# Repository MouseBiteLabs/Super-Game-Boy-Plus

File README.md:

# Super Game Boy Plus (SGB+) QOL/Bugfix Branch

[MouseBiteLabs](https://github.com/MouseBiteLabs) designed a neat retro hardware project, the [Super Game Boy Plus](https://github.com/MouseBiteLabs/Super-Game-Boy-Plus) that took the proprietary components from a Super Game Boy and allowed the user to not only install a 4.194MHz crystal to fix the timing issues the 4.295MHz clock from the SNES introduced, but also to allow the user to Over- and Under-clock the system at will using button presses.  I thought that was brilliant, but a few things stood out to me.

- First, I prefer to use an 8bitdo SN30 controller, and one of the things that this controller does is allow the user to turn it off by holding [START] for several seconds.  This conflicts with the SGB+ clock alteration function.
- Secondly, the length of time necessary to hold the buttons was flow-breaking; having to hold [SELECT], wait a second, and then hold [START] for another second was _annoying_.  Plus, the 'hold to fast-forward/rewind' thing is cute, but not really meaningful when you only have a couple of clockdivs one way or the other.
- Thirdly, there is a bug or oversight in the original firmware, where employing the Clock Reset function (holding both [SELECT] and [START] for 5 seconds resets the clock to baseline) causes that state to be persistent - use it, and you won't be able to alter clock timing until you power cycle the SGB+.

Neither of these first two are _critical issues_, but I think they can be much more user-friendly.  The third is definitely an annoyance.

In this fork, I've included the original project files, as well as **SGB_Clock_Control_Tap_ALTERED.ino**, which can be written to an ATTINY85 using an AVR-capable Arduino Uno (my recommendation is the r3 Uno; don't make the same mistake I did and grab the Uno Q - it's ARM-based and can't address ATTINY stuff as a programmer).

The chief differences in my **SGB_Clock_Control_Tap_ALTERED.ino** file:

- Over/Underclock done by holding [SELECT/START] and _tapping_ the other.
- Clock Reset timing reduced to 2500ms from 5000ms.
- Clock Reset no longer continuously triggers once activated; once Clock Reset occurs, it resets itself, allowing for as much time-based shenanigans as one would care.

- Full credit for the project, design, and the vast majority of the code go to [MouseBiteLabs](https://github.com/MouseBiteLabs); all I did was riff on his project and fix a few things to my liking.

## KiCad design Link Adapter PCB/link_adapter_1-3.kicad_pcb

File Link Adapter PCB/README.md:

# Link Adapter PCB

Use this board to center the link port properly in SNES shells that *aren't* the SGB2.

NOTE: This only works on the North American Super Game Boy shell. It will not fit in a Super Famicom or PAL region SGB.

## Board Characteristics and Order Information

The zipped folder contains all the gerber files for this board. The board characteristics don't really matter a whole lot, but I would err on the thicker side for support purposes.

- Thickness: any
- Layers: 2
- Surface Finish: any

<a href="https://oshpark.com/shared_projects/MZ2FDhuA">Also available on OSH Park.</a>

## Board Explanation

Please review the main guide for instructions on how to install the board. Here is a quick reference for the board to help you keep it straight, and to not install it incorrectly.

## License

<br />This work is licensed under a <a rel="license" href="http://creativecommons.org/licenses/by-sa/4.0/">Creative Commons Attribution-ShareAlike 4.0 International License</a>. You are able to copy and redistribute the material in any medium or format, as well as remix, transform, or build upon the material for any purpose (even commercial) - but you **must** give appropriate credit, provide a link to the license, and indicate if any changes were made.

©MouseBiteLabs 2024

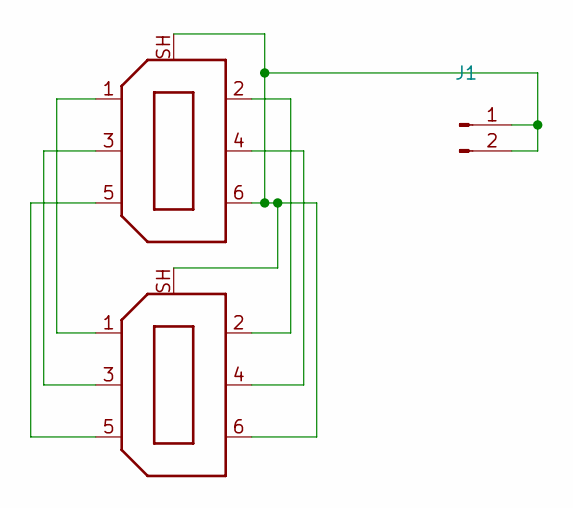
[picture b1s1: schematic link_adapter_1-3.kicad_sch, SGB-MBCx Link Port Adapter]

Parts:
J1: Conn_01x02_Pin; PinHeader_1x02_P2.54mm_Vertical
P1, P2: LINKPORTCGB-LINK; GameBoy_LinkPort_MGB_Horizontal

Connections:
unnamed: J1.1, J1.2, P1.6 (GND), P1.SH, P2.6 (GND), P2.SH
unnamed: P1.1 (+5V), P2.1 (+5V)
unnamed: P1.5 (CLK), P2.5 (CLK)
unnamed: P1.3 (IN), P2.3 (IN)
unnamed: P1.2 (OUT), P2.2 (OUT)
unnamed: P1.4 (SD), P2.4 (SD)

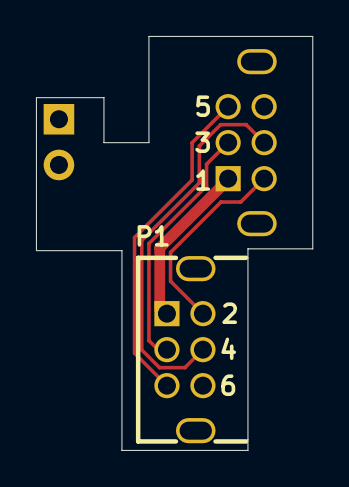
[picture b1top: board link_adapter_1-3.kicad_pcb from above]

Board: 2 copper layers, 15.3 x 23.0 mm, 3 parts (1 on the bottom side), 6 nets.

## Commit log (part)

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2024-09-08 Rename README.md to README.md
2025-04-08 Remove a double space
    Fixed a crucial double space mishap in the header of the Group E components table
